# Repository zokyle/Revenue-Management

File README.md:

# Revenue-Management

Two independent FastAPI applications share this repository and its Python
dependencies:

| App | Directory | Run | What it does |
|-----|-----------|-----|--------------|
| Hotel revenue management | `app/` | `uvicorn app.main:app --reload` | demand forecasting, dynamic pricing, overbooking, PMS integrations |
| **Caddie** - golf strategy agent | `golf/` | `uvicorn golf.main:app --reload --port 8001` | learns your golf game from logged rounds and builds hole-by-hole strategies for any course, with the goal of breaking 80 |

```bash
pip install -r requirements.txt
cp .env.example .env
python scripts/seed_golf.py      # demo golfer, course and 12 rounds for the golf app
python -m pytest -q              # both apps' test suites
```

See [`golf/README.md`](golf/README.md) for how the golf agent works (with
pictures and analogies), the data-collection workflow, and the API.

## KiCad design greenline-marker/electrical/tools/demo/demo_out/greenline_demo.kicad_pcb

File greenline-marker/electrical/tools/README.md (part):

# gleda - GreenLine scripted EDA toolchain

`gleda` turns a "netlist as code" design description (Python) into a verified
KiCad 7 board.  KiCad's own DRC is the judge; nothing is reported as passing
unless KiCad says so.

The flow, each step a module that can be used on its own:

```
design script (Python)  ->  checks  ->  board  ->  router  ->  zone fill + KiCad DRC
                                                                     |
                 schematic + netlist round trip   <-   outputs (Gerber, drill, BOM,
                                                       pick-and-place, renders, JSON)
```

This file documents the design model, the checks, footprints, the board
builder, the DRC runner, the **router**, the **outputs**, the **schematic
generator** and the **demo build**, each with its limits.  Two sections are
written to be read on their own: **[Quick start: authoring a new
design](#quick-start-authoring-a-new-design)** and
**[Limitations](#limitations)** (everything the toolchain does not do, in one
place).

```
tools/
  gleda/
    model.py       design description (pure Python, no pcbnew)
    coords.py      THE design <-> KiCad coordinate conversion
    geometry.py    outline paths/polygons, placed pads, courtyards (shapely)
    footprints.py  programmatic footprints + KiCad library wrappers
    checks.py      ERC-style and placement checks
    board.py       .kicad_pcb / .kicad_pro / .kicad_dru generation, routing
                   primitives in/out, via tenting
    drc.py         zone fill + KiCad DRC + report parser + pass/fail policy
    kicad_cli.py   kicad-cli wrapper, SVG export, SVG reader
    router.py      autorouter (escape stage, negotiated routing, end game,
                   cleanup, exact audit, plane-fill prediction)
    raster.py      routing grid and exact obstacle rasterisation
    _astar.py      A* search kernel (numba-compiled when numba is installed)
    routeplot.py   quick matplotlib picture of a routed design (debug aid)
    outputs.py     Gerbers, drill, pick-and-place, BOM, netlist / mechanical JSON,
                   renders, fab README + zip - each checked against the model
    schematic.py   KiCad 7 schematic (one sheet per group), PDF, netlist round trip
  demo/
    quickstart_board.py  the smallest complete design + the whole flow (start here)
    demo_design.py     the GreenLine DEMO board (stand-in for the real GL-1)
    build_demo.py      checks -> board -> route -> DRC -> outputs -> schematic
    demo_out/          everything the last demo build produced
  tests/           pytest suite (run it from tools/)
    mini_design.py     round 30 mm fixture (castellated module, cutout, notch, slot)
    dshape_design.py   GreenLine-shaped fixture (D outline, LQFP-64, two BGAs,
                       bottom LED ring + contact row, fine net class)
    proof_core.py      builds both, KiCad DRC, plots, orientation proof
    proof_out/         outputs of the last proof run
```

## Requirements

KiCad 7.0.x with its Python module.  Always use the system interpreter:

```
cd electrical/tools
/usr/bin/python3 -m pytest -q            # test suite (about 2 minutes)
/usr/bin/python3 -m pytest -q --runslow  # ... plus the demo build from nothing (5 to 6 minutes in all)
/usr/bin/python3 demo/build_demo.py      # the whole flow on the demo board, exit 0 only if
                                         # checks, routing, KiCad DRC and round trip all pass
/usr/bin/python3 tests/proof_core.py     # build + DRC + render both reference boards
/usr/bin/python3 -m gleda.drc out/board.kicad_pcb [--allow-unconnected]
```

`pdftoppm` / `pdfinfo` (poppler-utils) turn KiCad's PDF plots into PNGs; numba
makes the router usable on real boards.  No GUI is ever started and nothing
is downloaded.

## The whole flow in one script

```python
import sys; sys.path.insert(0, "electrical/tools")
from gleda import checks, board, router, drc, outputs, schematic

design = my_design()                                    # a gleda.model.Design, see below

checks.run_checks(design).raise_if_errors()             # ERC-style + placement checks
files = board.build_board(design, "out")                # .kicad_pcb / .kicad_pro / .kicad_dru
result = router.route(design)                           # RouteResult; .complete, .unrouted
board.apply_routing(files.pcb, result.tracks, result.vias, via_tenting=design.via_tenting)
res = drc.run_drc(files.pcb, json_path="out/drc.json")  # zone fill + KiCad DRC
drc.assert_clean(res)                                   # 0 errors, 0 unconnected - or DrcError
package = outputs.generate_outputs(design, files.pcb, "out", drc_result=res, vias=result.vias)
assert package.ok, package.problems                     # plotted data == design model
sch = schematic.generate_schematic(design, "out")       # <name>.kicad_sch + one sheet per group
schematic.export_pdf(sch.root, "out/schematic.pdf")
trip = schematic.round_trip(design, sch.root)           # KiCad's netlist vs the model
assert trip.ok, trip.problems
```

`demo/build_demo.py` is exactly this with reporting around it.

## Quick start: authoring a new design

A design is one Python function that returns a `gleda.model.Design`; a second
short function takes it through the flow.  **Start from
`demo/quickstart_board.py`**: 135 lines, one 16-ball 0.5 mm BGA with its
capacitor, a pull-up and a contact row on a 24 mm D-shaped board, every step
below in the order one writes it, and a `build(design, out)` function that is
the whole flow with honest exit codes.  The test suite runs it, so it works as
written:

```
cd electrical/tools
/usr/bin/python3 demo/quickstart_board.py /some/empty/dir     # about 10 s
#   gleda checks for quickstart: 0 error(s), 0 warning(s)
#   routed 16/16 connections (100.0 %) of 10 nets, 102 tracks, 16 vias, 126.6 mm, 0 audit violation(s)
#   KiCad DRC: 0 error(s), 0 unconnected, 0 warning(s)
#   outputs: 34 files, 0 problem(s) against the model
#   netlist round trip matches: 10 nets, 26 pads, 4 components, 4 unconnected pins
```

`demo/demo_design.py` and `demo/build_demo.py` are the same thing at the size
of the real board (100 parts), with stage reporting around it.

1. **Outline and rules.**  `Outline(PathShape.d_shape(r, flat_y))` (or
   `Circle`, `RoundedPolygon`, any line + arc `PathShape`), then
   `add_hole` / `add_npth_slot` / `add_cutout`.  `Design(name, outline,
   layers=4, rules=US_4L_STD, board_thickness=0.8)`; use `US_4L_FINE` (board
   minimums 0.09 / 0.09 mm) only if a fine-pitch BGA forces it.
2. **Net classes.**  `Default` (0.15 / 0.127) and `Power` (0.30 / 0.127)
   exist.  Add `d.add_netclass("Fine", track_width=0.09, clearance=0.09)` for
   the nets on the inner balls of a 0.5 mm BGA and **declare where it may be
   fine**: `d.add_fine_area("U2", margin=5.0)`.  Outside the fine areas those
   nets are routed and DRC-checked at the standard 0.15 / 0.127 mm.  Try this
   first; if the router cannot finish that way (it cannot on the demo board),
   remove the fine areas - the fine tracks may then run anywhere on those
   nets, the checks warn, the router widens what it can, and the fab README
   tells the fab to quote the whole board at 0.09 / 0.09 mm.
3. **Parts.**  `d.add(Part(ref, value, footprint, pins=..., mpn=...,
   manufacturer=..., distributor=..., distributor_pn=..., unit_price=...,
   x=..., y=..., rotation=..., side="top" | "bottom", height_mm=...,
   group="sheet name"))`.  `footprint` is a KiCad `"Lib:Name"` string or a
   generator from `gleda.footprints` (`bga`, `quad_package`, `two_pad`,
   `pad_row`, `test_pad`, `battery_tab`, `fpc_connector`,
   `castellated_module` ...).  `pins` maps pin name -> pad number(s) and
   electrical type.  Bare pads and tabs get `in_bom=False`.
4. **Nets.**  `d.net("NAME", "U1.PA5", "R3.1", netclass="Power")`; every pin
   must be on a net, be of type `nc` or be listed in `d.no_connect(...)`.
   Supplies fed from outside the netlist get `power_flag=True`.
5. **Planes, keep-outs, mechanics.**  `d.add_plane("GND", "In1.Cu")`,
   `d.add_plane("V2V8", "In2.Cu", routable=True)` (plane and third routing
   layer), `d.add_body_keepout("U4")` (no copper under a MEMS body),
   `d.add_keepout(shape, layers=..., tracks=..., vias=..., copper=...,
   footprints=...)` (for example `tracks=False, vias=True` over a wetted
   area: no via holes there), `d.add_placement_keepout`, `d.add_height_limit`.
6. **Fab and assembly details.**  `d.via_tenting = "bottom"`,
   `d.via_protection = "plugged from the bottom side (IPC-4761 type III-a)"`,
   `d.fab_notes.append("...")`, three `d.add_fiducial(x, y, side=...)` per
   assembled side.
7. **Run the checks until they are clean**: `print(checks.run_checks(d).text())`.
   Errors stop the flow; read the warnings (`fine_unconfined`, `no_fiducials`,
   `plane_partial`, `decoupling_far` ...).
8. **Build, route, judge, export** - the script under "The whole flow in one
   script" above.  The router's result is honest (`result.complete`,
   `result.unrouted`, `result.warnings`); KiCad's DRC decides
   (`drc.assert_clean`); `outputs.generate_outputs` refuses a board that is
   not clean and verifies what it plotted against the model.

What makes a board routable by THIS router (learned on the demo, see the end
of this file): pins of a fixed-function part on the side that faces their
destination; about 1.4 x 2.0 mm per 0402 that needs a plane via; the sides of
a BGA that face the rest of the circuit kept clear for the bus escape; nothing
in the pocket between a hole and the next part; fiducials and fine areas
placed before routing (both take routing room).

**The first mistake everybody makes**: an inner ball of a 0.5 mm-pitch BGA on
a net whose class is wider than 0.09 mm (`Default`, `Power`).  Only a 0.09 mm
track with 0.09 mm clearance passes between two 0.23 mm balls, a via does not
fit between them and vias are never put in pads - so such a ball cannot be
reached, whatever net it is on, GND included.  Put every net that touches an
inner ball into a fine class (the demo: `Fine` for signals, `CamPower`
0.15 / 0.09 for supply balls on the outer ring), give the BGA pads
`pad_clearance=0.09`, and keep supplies on the outer ring where the ball map
lets you.  The router does not hang on it and does not pretend:

```
routed 15/16 connections (93.8 %) of 10 nets, 83 tracks, 15 vias, ...
OPEN D0: [['J1.3'], ['U1.B2']]  [no path from U1.B2 to J1.3]
```

A net the router leaves open is always reported like this
(`result.unrouted` -> `Unrouted.net`, `.pieces`, `.reason`; per connection in
`result.failures`) and `result.complete` is False.  Move a part or a pin,
change the class, and run again - or route that net by hand in KiCad and mark
it `no_route=True`.

## Conventions (read this first)

* Units are millimetres.  The design origin is the **board centre** (for the
  D-shaped board: the centre of the circle), **+x is right, +y is up** as seen
  from the top of the board; rotation is counter-clockwise positive.
* KiCad's y axis points down.  The conversion happens in exactly one module,
  `gleda/coords.py` (`to_kicad_mm`, `from_kicad_mm`, ...).  The board centre is
  placed at (100, 100) mm on the KiCad page and the board's auxiliary
  (drill/place) origin is set to the same point.
* Footprint-local coordinates (custom footprints, `FootprintGeom`) use the
  same handedness: +y up, looking at the component side.
* **Bottom-side parts** follow KiCad's native definition, so `Part.rotation`
  is the number KiCad stores, shows and writes to position files:
  the footprint is flipped about its local X axis and then rotated CCW as
  seen from the top:

      top:     board = (x, y) + R(rotation) . (lx,  ly)
      bottom:  board = (x, y) + R(rotation) . (lx, -ly)

  `coords.local_to_board()` implements this and
  `tests/test_board.py::test_pads_match_model_geometry` proves that every pad
  position predicted by the model equals what pcbnew reports for the saved
  board.  `tests/test_board.py::test_top_view_svg_has_plus_y_up` proves from a
  KiCad SVG plot that a part placed at +y is drawn toward the top.

## Describing a design

```python
from gleda.model import (Design, Outline, Circle, RoundedPolygon, PathShape, Part,
                         two_pin, n_pin, US_4L_FINE, BOTTOM)
from gleda import footprints as F

# circle r = 21.2 mm about the origin, clipped by the chord y = +17.3 mm
outline = Outline(PathShape.d_shape(21.2, 17.3))
# also: Outline(Circle(0, 0, 19.0)), RoundedPolygon(...), any line + arc path:
#   PathShape.begin(-5, 0).line_to(5, 0).arc_to(-5, 0, 0, 0, ccw=True).close()
#   PathShape.clipped_circle(0, 0, 21.2, [(90, 17.3), (270, 19.0)])
outline.add_cutout(Circle(9.0, 0.0, 6.5))              # internal routed cutout
outline.add_notch(RoundedPolygon.rect(0, -21.2, 3, 2, 0.4))   # crosses the edge
outline.add_slot(-6, -11, -4, -11, 0.8)
outline.add_hole(-12, 5, 1.2)                          # NPTH

d = Design("greenline", outline, layers=4, rules=US_4L_FINE, board_thickness=0.8)
d.add_netclass("Fine", track_width=0.09, clearance=0.09)   # BGA escape only
d.via_tenting = "bottom"                               # "both" (default) | "bottom" | "top" | "none"
d.via_protection = "plugged from the bottom side (IPC-4761 type III-a)"   # -> fab README
d.fab_notes.append("The bottom side is a wetted surface: no open via holes there.")

cam = F.bga("Cam_BGA25", 5, 5, pitch=0.5, pad_d=0.23, body=(3.47, 2.95), height=2.76,
            pad_clearance=0.09, courtyard_margin=0.2)
d.add(Part("U2", "Camera", cam,
           pins={"D0": ("B2", "bidir"), "AVDD": ("C5", "power_in"),
                 "GND": (("E2", "E3", "E4"), "power_in"), "NC": ("A1", "nc")},  # ... all balls
           mpn="...", manufacturer="...", distributor="Digi-Key", distributor_pn="...",
           unit_price=6.0, x=-10.2, y=15.6, rotation=0, side="top", height_mm=2.76,
           group="camera"))
d.add(Part("C1", "100n", "Capacitor_SMD:C_0402_1005Metric", pins=two_pin(),
           mpn="...", x=-7.2, y=15.3, rotation=90, group="camera"))
d.add(Part("J2", "Cradle pads", F.pad_row("ContactRow", 7, 2.54, 1.8), pins=n_pin(7),
           x=0, y=-17.0, side=BOTTOM, in_bom=False))    # bare pads on the bottom

d.net("GND", "U2.GND", "C1.2", "J2.4", netclass="Power")
d.net("V2V8", "U2.AVDD", "C1.1", netclass="Power", power_flag=True)
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
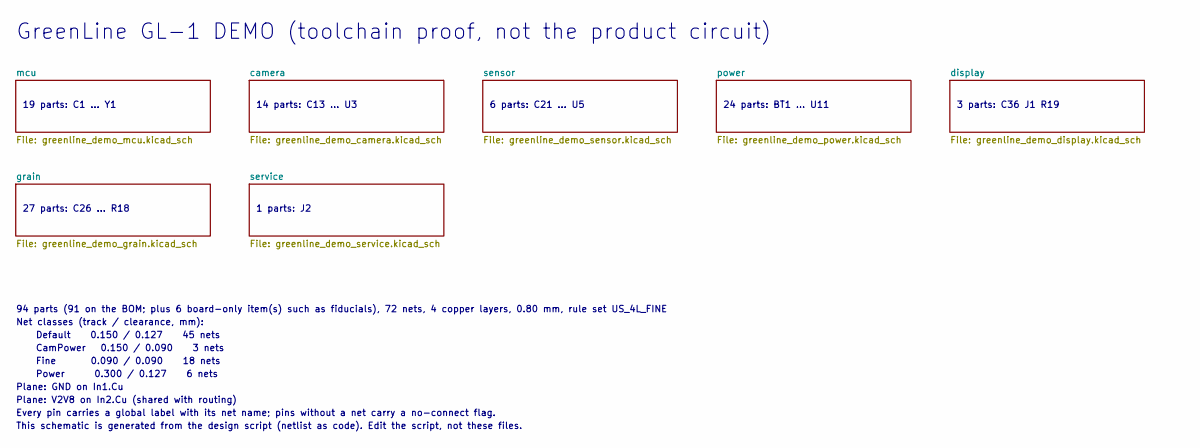
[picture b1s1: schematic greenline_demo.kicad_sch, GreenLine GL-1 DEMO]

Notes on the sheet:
GreenLine GL-1 DEMO (toolchain proof, not the product circuit)
19 parts: C1 ... Y1
14 parts: C13 ... U3
6 parts: C21 ... U5
24 parts: BT1 ... U11
3 parts: C36 J1 R19
27 parts: C26 ... R18
1 parts: J2
94 parts (91 on the BOM; plus 6 board-only item(s) such as fiducials), 72 nets, 4 copper layers, 0.80 mm, rule set US_4L_FINE
Net classes (track / clearance, mm):
Default 0.150 / 0.127 45 nets
CamPower 0.150 / 0.090 3 nets
Fine 0.090 / 0.090 18 nets
Power 0.300 / 0.127 6 nets
Plane: GND on In1.Cu
Plane: V2V8 on In2.Cu (shared with routing)
Every pin carries a global label with its net name; pins without a net carry a no-connect flag.
This schematic is generated from the design script (netlist as code). Edit the script, not these files.

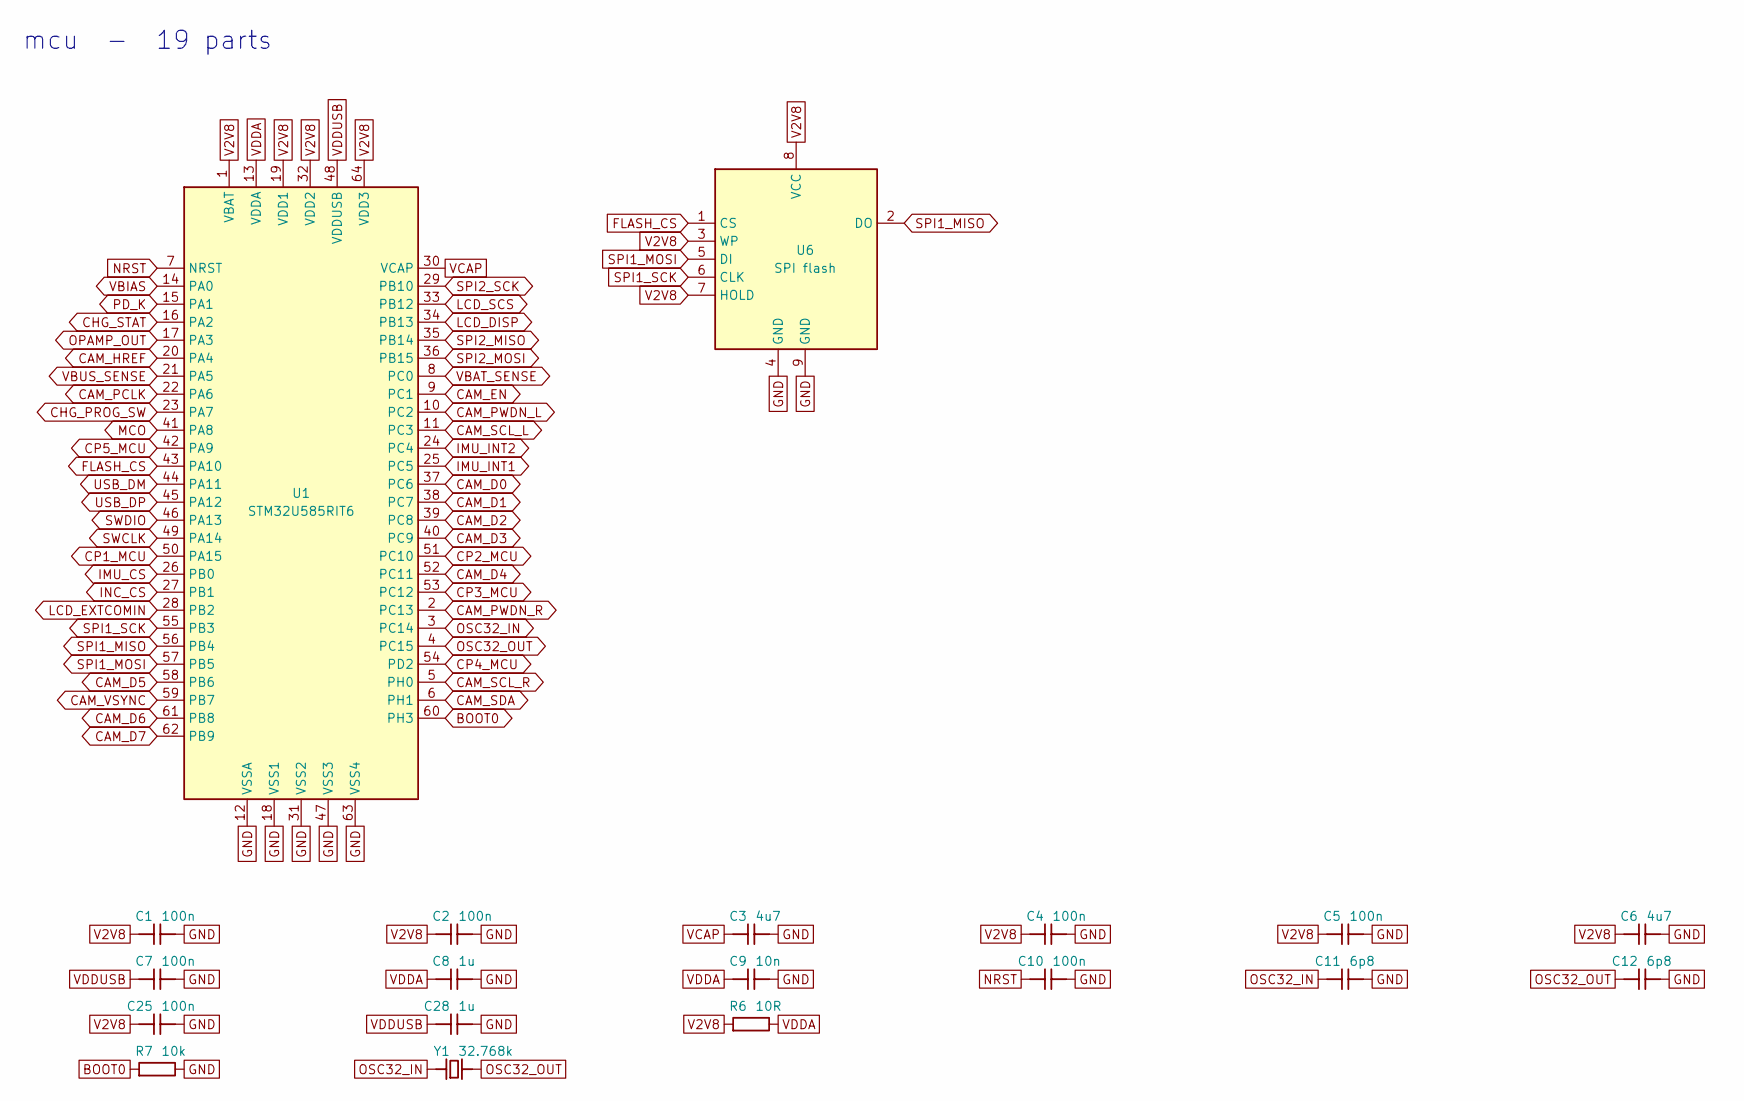
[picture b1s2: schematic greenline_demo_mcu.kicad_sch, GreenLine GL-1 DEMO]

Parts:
C1, C2, C4, C5, C7, C10, C25: 100n; C_0402_1005Metric; MPN GRM155R71C104KA88D
C3, C6: 4u7; C_0402_1005Metric; MPN GRM155R60J475ME47D
C8, C28: 1u; C_0402_1005Metric; MPN GRM155R61A105KE15D
C9: 10n; C_0402_1005Metric; MPN GRM155R71H103KA88D
C11, C12: 6p8; C_0402_1005Metric; MPN GRM1555C1H6R8CA01D
R6: 10R; R_0402_1005Metric; MPN RC0402FR-0710RL
R7: 10k; R_0402_1005Metric; MPN RC0402FR-0710KL
U1: STM32U585RIT6; LQFP-64_10x10mm_P0.5mm; MPN STM32U585RIT6
U6: SPI flash; WSON-8-1EP_6x5mm_P1.27mm_EP3.4x4.3mm; MPN MX25R6435FZNIL0
Y1: 32.768k; Crystal_SMD_3215-2Pin_3.2x1.5mm; MPN ABS07-120-32.768KHZ-T

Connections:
BOOT0: R7.1, U1.60 (PH3)
CAM_D0: U1.37 (PC6); also elsewhere on the board
CAM_D1: U1.38 (PC7); also elsewhere on the board
CAM_D2: U1.39 (PC8); also elsewhere on the board
CAM_D3: U1.40 (PC9); also elsewhere on the board
CAM_D4: U1.52 (PC11); also elsewhere on the board
CAM_D5: U1.58 (PB6); also elsewhere on the board
CAM_D6: U1.61 (PB8); also elsewhere on the board
CAM_D7: U1.62 (PB9); also elsewhere on the board
CAM_EN: U1.9 (PC1); also elsewhere on the board
CAM_HREF: U1.20 (PA4); also elsewhere on the board
CAM_PCLK: U1.22 (PA6); also elsewhere on the board
CAM_PWDN_L: U1.10 (PC2); also elsewhere on the board
CAM_PWDN_R: U1.2 (PC13); also elsewhere on the board
CAM_SCL_L: U1.11 (PC3); also elsewhere on the board
CAM_SCL_R: U1.5 (PH0); also elsewhere on the board
CAM_SDA: U1.6 (PH1); also elsewhere on the board
CAM_VSYNC: U1.59 (PB7); also elsewhere on the board
CHG_PROG_SW: U1.23 (PA7); also elsewhere on the board
CHG_STAT: U1.16 (PA2); also elsewhere on the board
CP1_MCU: U1.50 (PA15); also elsewhere on the board
CP2_MCU: U1.51 (PC10); also elsewhere on the board
CP3_MCU: U1.53 (PC12); also elsewhere on the board
CP4_MCU: U1.54 (PD2); also elsewhere on the board
CP5_MCU: U1.42 (PA9); also elsewhere on the board
FLASH_CS: U1.43 (PA10), U6.1 (CS)
GND: C1.2, C2.2, C3.2, C4.2, C5.2, C6.2, C7.2, C8.2, C9.2, C10.2, C11.2, C12.2, C25.2, C28.2, R7.2, U1.12 (VSSA), U1.18 (VSS1), U1.31 (VSS2), U1.47 (VSS3), U1.63 (VSS4), U6.4 (GND), U6.9 (GND); also elsewhere on the board
IMU_CS: U1.26 (PB0); also elsewhere on the board
IMU_INT1: U1.25 (PC5); also elsewhere on the board
IMU_INT2: U1.24 (PC4); also elsewhere on the board
INC_CS: U1.27 (PB1); also elsewhere on the board
LCD_DISP: U1.34 (PB13); also elsewhere on the board
LCD_EXTCOMIN: U1.28 (PB2); also elsewhere on the board
LCD_SCS: U1.33 (PB12); also elsewhere on the board
MCO: U1.41 (PA8); also elsewhere on the board
NRST: C10.1, U1.7 (NRST); also elsewhere on the board
OPAMP_OUT: U1.17 (PA3); also elsewhere on the board
OSC32_IN: C11.1, U1.3 (PC14), Y1.1
OSC32_OUT: C12.1, U1.4 (PC15), Y1.2
PD_K: U1.15 (PA1); also elsewhere on the board
SPI1_MISO: U1.56 (PB4), U6.2 (DO)
SPI1_MOSI: U1.57 (PB5), U6.5 (DI); also elsewhere on the board
SPI1_SCK: U1.55 (PB3), U6.6 (CLK); also elsewhere on the board
SPI2_MISO: U1.35 (PB14); also elsewhere on the board
SPI2_MOSI: U1.36 (PB15); also elsewhere on the board
SPI2_SCK: U1.29 (PB10); also elsewhere on the board
SWCLK: U1.49 (PA14); also elsewhere on the board
SWDIO: U1.46 (PA13); also elsewhere on the board
USB_DM: U1.44 (PA11); also elsewhere on the board
USB_DP: U1.45 (PA12); also elsewhere on the board
V2V8: C1.1, C2.1, C4.1, C5.1, C6.1, C25.1, R6.1, U1.1 (VBAT), U1.19 (VDD1), U1.32 (VDD2), U1.64 (VDD3), U6.3 (WP), U6.7 (HOLD), U6.8 (VCC); also elsewhere on the board
VBAT_SENSE: U1.8 (PC0); also elsewhere on the board
VBIAS: U1.14 (PA0); also elsewhere on the board
VBUS_SENSE: U1.21 (PA5); also elsewhere on the board
VCAP: C3.1, U1.30 (VCAP)
VDDA: C8.1, C9.1, R6.2, U1.13 (VDDA)
VDDUSB: C7.1, C28.1, U1.48 (VDDUSB); also elsewhere on the board

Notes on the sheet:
mcu - 19 parts

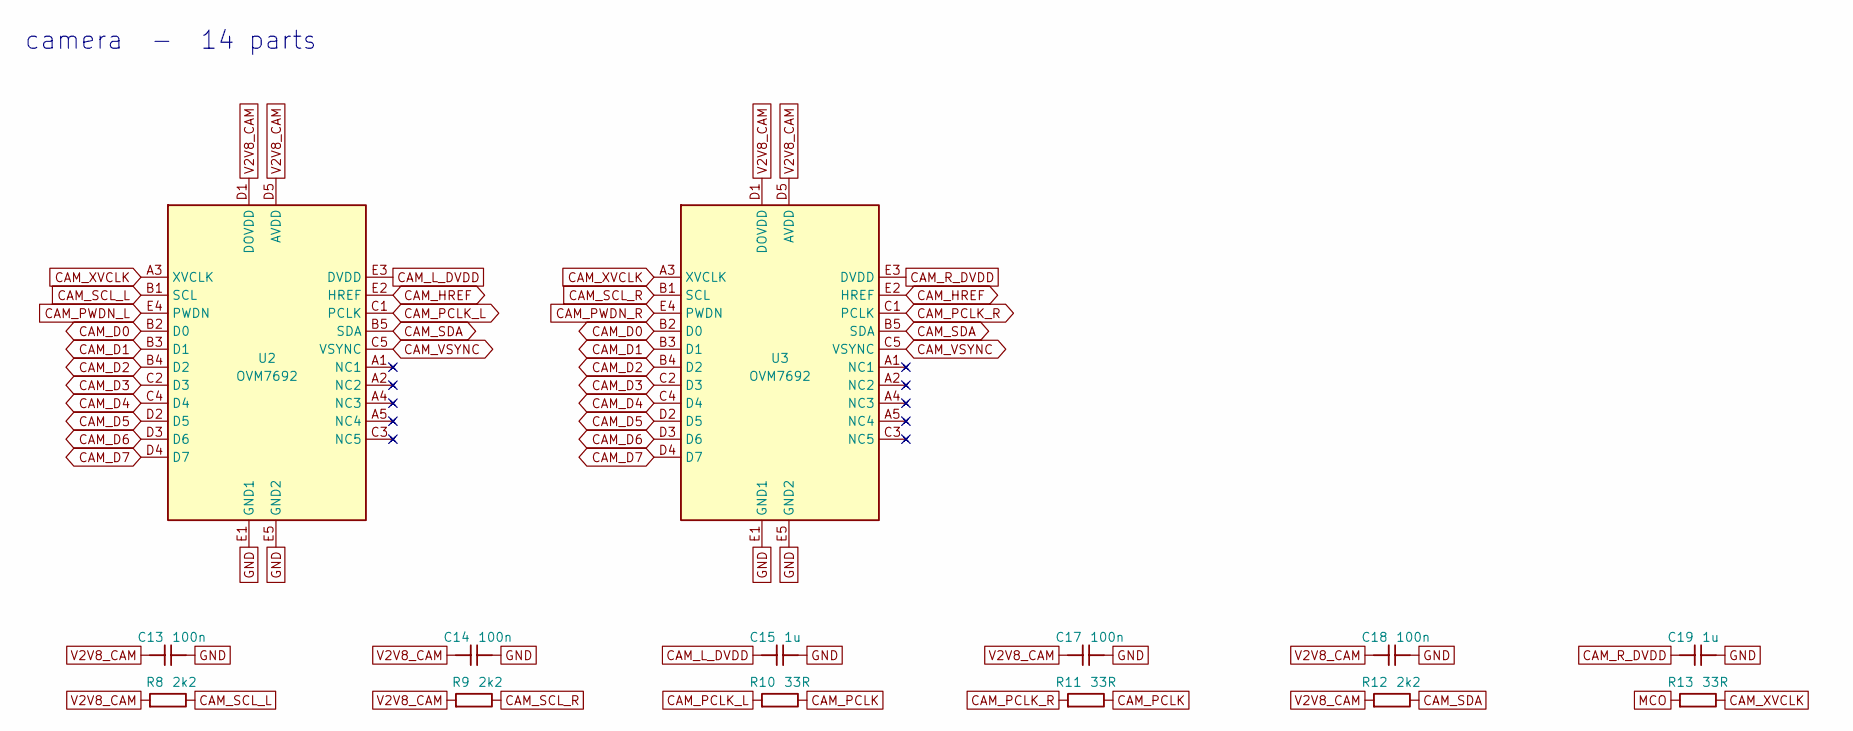
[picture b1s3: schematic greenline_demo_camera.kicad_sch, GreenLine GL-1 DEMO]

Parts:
C13, C14, C17, C18: 100n; C_0402_1005Metric; MPN GRM155R71C104KA88D
C15, C19: 1u; C_0402_1005Metric; MPN GRM155R61A105KE15D
R8, R9, R12: 2k2; R_0402_1005Metric; MPN RC0402FR-072K2L
R10, R11, R13: 33R; R_0402_1005Metric; MPN RC0402FR-0733RL
U2, U3: OVM7692; CamCube_BGA25_P0.5; MPN OVM7692-RYAA

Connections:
CAM_D0: U2.B2 (D0), U3.B2 (D0); also elsewhere on the board
CAM_D1: U2.B3 (D1), U3.B3 (D1); also elsewhere on the board
CAM_D2: U2.B4 (D2), U3.B4 (D2); also elsewhere on the board
CAM_D3: U2.C2 (D3), U3.C2 (D3); also elsewhere on the board
CAM_D4: U2.C4 (D4), U3.C4 (D4); also elsewhere on the board
CAM_D5: U2.D2 (D5), U3.D2 (D5); also elsewhere on the board
CAM_D6: U2.D3 (D6), U3.D3 (D6); also elsewhere on the board
CAM_D7: U2.D4 (D7), U3.D4 (D7); also elsewhere on the board
CAM_HREF: U2.E2 (HREF), U3.E2 (HREF); also elsewhere on the board
CAM_L_DVDD: C15.1, U2.E3 (DVDD)
CAM_PCLK: R10.2, R11.2; also elsewhere on the board
CAM_PCLK_L: R10.1, U2.C1 (PCLK)
CAM_PCLK_R: R11.1, U3.C1 (PCLK)
CAM_PWDN_L: U2.E4 (PWDN); also elsewhere on the board
CAM_PWDN_R: U3.E4 (PWDN); also elsewhere on the board
CAM_R_DVDD: C19.1, U3.E3 (DVDD)
CAM_SCL_L: R8.2, U2.B1 (SCL); also elsewhere on the board
CAM_SCL_R: R9.2, U3.B1 (SCL); also elsewhere on the board
CAM_SDA: R12.2, U2.B5 (SDA), U3.B5 (SDA); also elsewhere on the board
CAM_VSYNC: U2.C5 (VSYNC), U3.C5 (VSYNC); also elsewhere on the board
CAM_XVCLK: R13.2, U2.A3 (XVCLK), U3.A3 (XVCLK)
GND: C13.2, C14.2, C15.2, C17.2, C18.2, C19.2, U2.E1 (GND1), U2.E5 (GND2), U3.E1 (GND1), U3.E5 (GND2); also elsewhere on the board
MCO: R13.1; also elsewhere on the board
V2V8_CAM: C13.1, C14.1, C17.1, C18.1, R8.1, R9.1, R12.1, U2.D1 (DOVDD), U2.D5 (AVDD), U3.D1 (DOVDD), U3.D5 (AVDD); also elsewhere on the board

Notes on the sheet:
camera - 14 parts

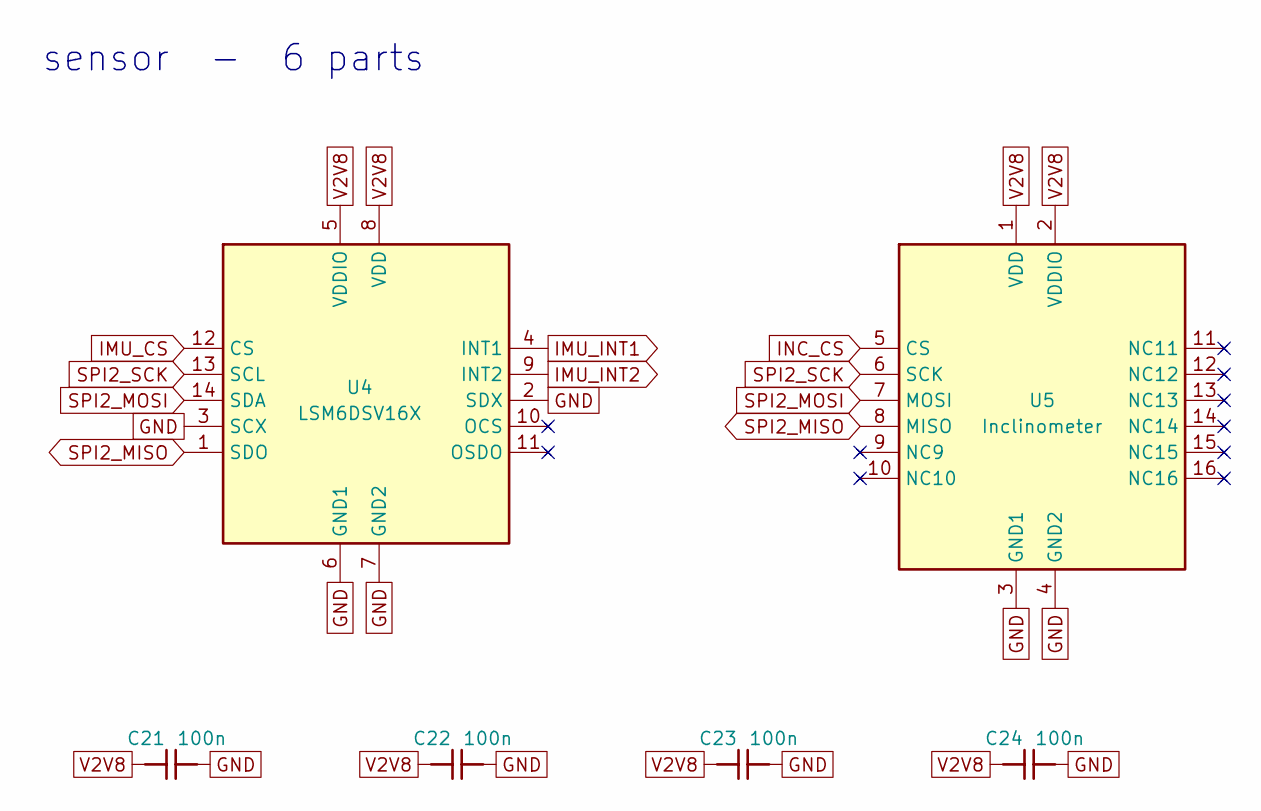
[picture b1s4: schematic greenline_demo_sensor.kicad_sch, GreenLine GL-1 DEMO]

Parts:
C21, C22, C23, C24: 100n; C_0402_1005Metric; MPN GRM155R71C104KA88D
U4: LSM6DSV16X; LGA-14_3x2.5mm_P0.5mm_LayoutBorder3x4y; MPN LSM6DSV16XTR
U5: Inclinometer; LGA-16_5x5mm_P1.0mm; MPN IIS2ICLXTR

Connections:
GND: C21.2, C22.2, C23.2, C24.2, U4.2 (SDX), U4.3 (SCX), U4.6 (GND1), U4.7 (GND2), U5.3 (GND1), U5.4 (GND2); also elsewhere on the board
IMU_CS: U4.12 (CS); also elsewhere on the board
IMU_INT1: U4.4 (INT1); also elsewhere on the board
IMU_INT2: U4.9 (INT2); also elsewhere on the board
INC_CS: U5.5 (CS); also elsewhere on the board
SPI2_MISO: U4.1 (SDO), U5.8 (MISO); also elsewhere on the board
SPI2_MOSI: U4.14 (SDA), U5.7 (MOSI); also elsewhere on the board
SPI2_SCK: U4.13 (SCL), U5.6 (SCK); also elsewhere on the board
V2V8: C21.1, C22.1, C23.1, C24.1, U4.5 (VDDIO), U4.8 (VDD), U5.1 (VDD), U5.2 (VDDIO); also elsewhere on the board

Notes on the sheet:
sensor - 6 parts

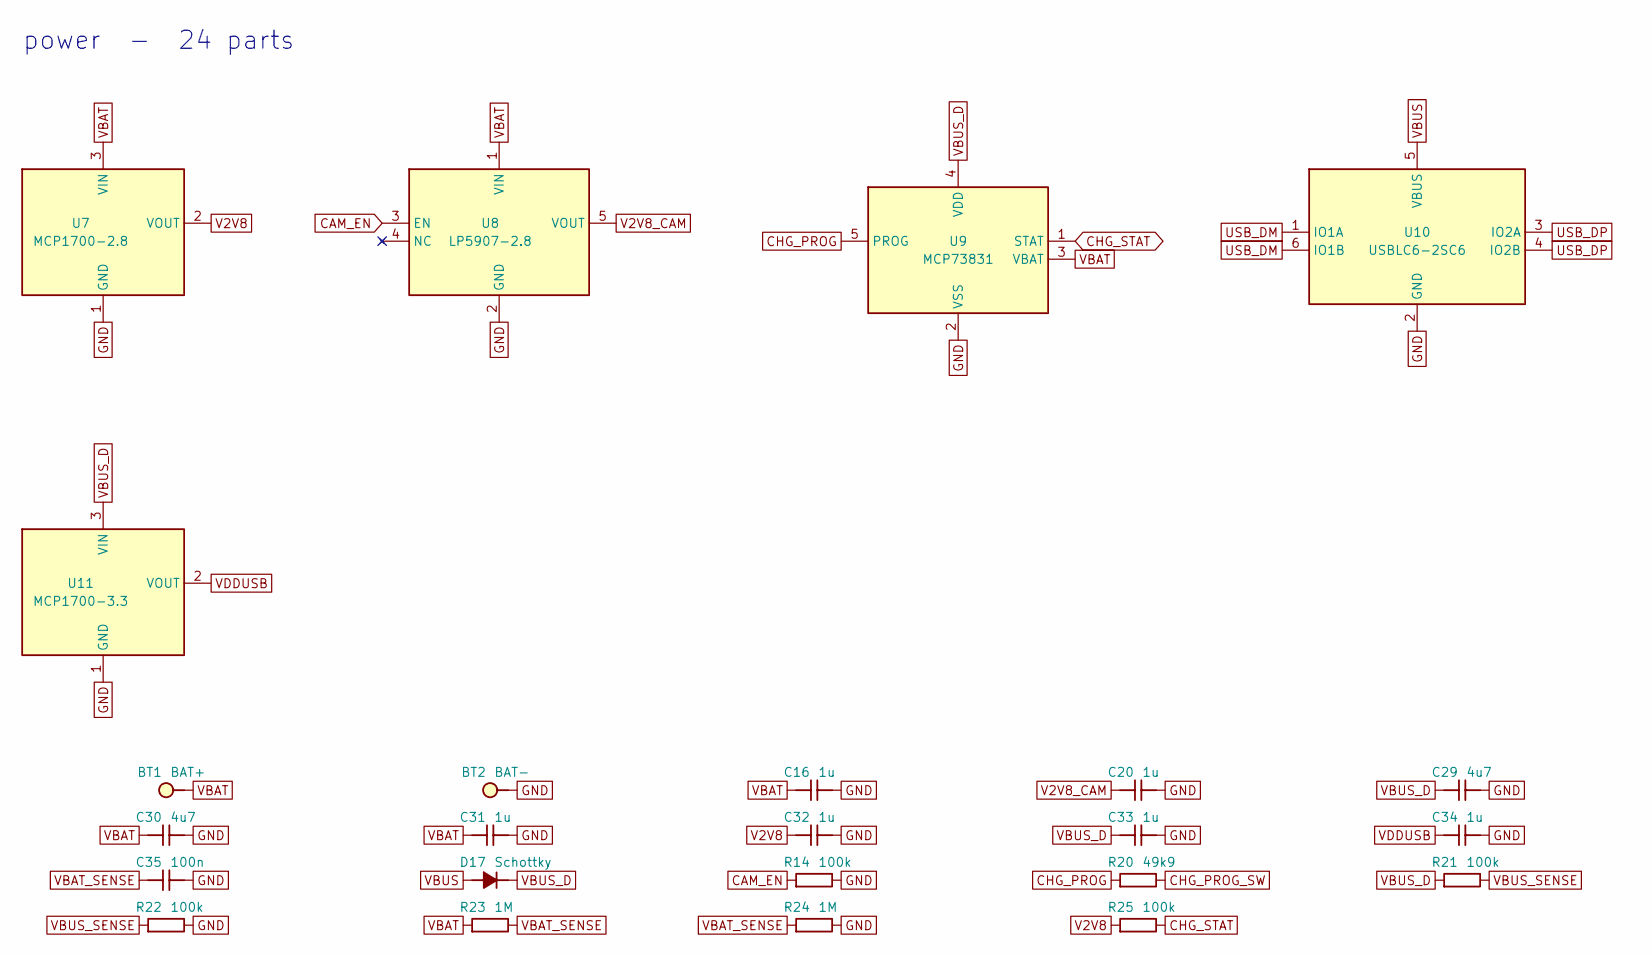
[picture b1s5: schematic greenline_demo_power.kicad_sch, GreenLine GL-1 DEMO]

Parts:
BT1: BAT+; BatteryTab_1.2x2mm
BT2: BAT-; BatteryTab_1.2x2mm
C16, C20, C31, C32, C33, C34: 1u; C_0402_1005Metric; MPN GRM155R61A105KE15D
C29, C30: 4u7; C_0402_1005Metric; MPN GRM155R60J475ME47D
C35: 100n; C_0402_1005Metric; MPN GRM155R71C104KA88D
D17: Schottky; D_SOD-323; MPN BAT60JFILM
R14, R21, R22, R25: 100k; R_0402_1005Metric; MPN RC0402FR-07100KL
R20: 49k9; R_0402_1005Metric; MPN RC0402FR-0749K9L
R23, R24: 1M; R_0402_1005Metric; MPN RC0402FR-071ML
U7: MCP1700-2.8; SOT-23; MPN MCP1700T-2802E/TT
U8: LP5907-2.8; SOT-23-5; MPN LP5907MFX-2.8/NOPB
U9: MCP73831; SOT-23-5; MPN MCP73831T-2ACI/OT
U10: USBLC6-2SC6; SOT-23-6; MPN USBLC6-2SC6
U11: MCP1700-3.3; SOT-23; MPN MCP1700T-3302E/TT

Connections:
CAM_EN: R14.1, U8.3 (EN); also elsewhere on the board
CHG_PROG: R20.1, U9.5 (PROG)
CHG_PROG_SW: R20.2; also elsewhere on the board
CHG_STAT: R25.2, U9.1 (STAT); also elsewhere on the board
GND: BT2.1, C16.2, C20.2, C29.2, C30.2, C31.2, C32.2, C33.2, C34.2, C35.2, R14.2, R22.2, R24.2, U7.1 (GND), U8.2 (GND), U9.2 (VSS), U10.2 (GND), U11.1 (GND); also elsewhere on the board
USB_DM: U10.1 (IO1A), U10.6 (IO1B); also elsewhere on the board
USB_DP: U10.3 (IO2A), U10.4 (IO2B); also elsewhere on the board
V2V8: C32.1, R25.1, U7.2 (VOUT); also elsewhere on the board
V2V8_CAM: C20.1, U8.5 (VOUT); also elsewhere on the board
VBAT: BT1.1, C16.1, C30.1, C31.1, R23.1, U7.3 (VIN), U8.1 (VIN), U9.3 (VBAT)
VBAT_SENSE: C35.1, R23.2, R24.1; also elsewhere on the board
VBUS: D17.2 (A), U10.5 (VBUS); also elsewhere on the board
VBUS_D: C29.1, C33.1, D17.1 (K), R21.1, U9.4 (VDD), U11.3 (VIN)
VBUS_SENSE: R21.2, R22.1; also elsewhere on the board
VDDUSB: C34.1, U11.2 (VOUT); also elsewhere on the board

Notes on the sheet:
power - 24 parts

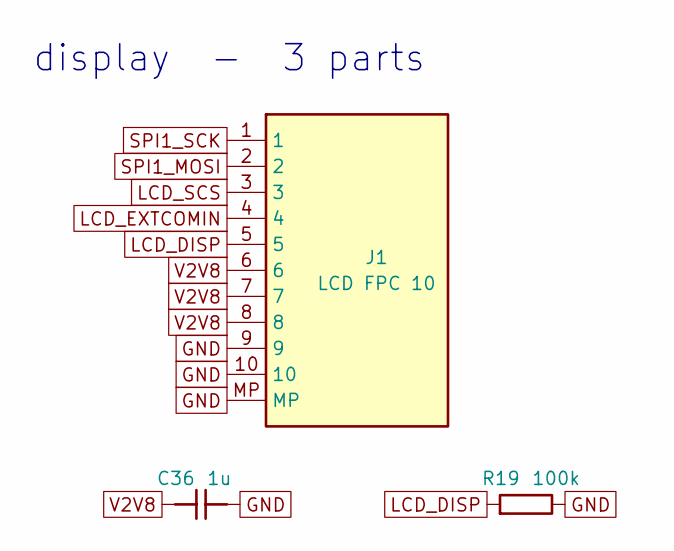
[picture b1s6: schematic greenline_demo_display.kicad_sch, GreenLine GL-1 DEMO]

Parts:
C36: 1u; C_0402_1005Metric; MPN GRM155R61A105KE15D
J1: LCD FPC 10; Hirose_FH12-10S-0.5SH_1x10-1MP_P0.50mm_Horizontal; MPN FH12A-10S-0.5SH(55)
R19: 100k; R_0402_1005Metric; MPN RC0402FR-07100KL

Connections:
GND: C36.2, J1.9, J1.10, J1.MP, R19.2; also elsewhere on the board
LCD_DISP: J1.5, R19.1; also elsewhere on the board
LCD_EXTCOMIN: J1.4; also elsewhere on the board
LCD_SCS: J1.3; also elsewhere on the board
SPI1_MOSI: J1.2; also elsewhere on the board
SPI1_SCK: J1.1; also elsewhere on the board
V2V8: C36.1, J1.6, J1.7, J1.8; also elsewhere on the board

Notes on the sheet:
display - 3 parts

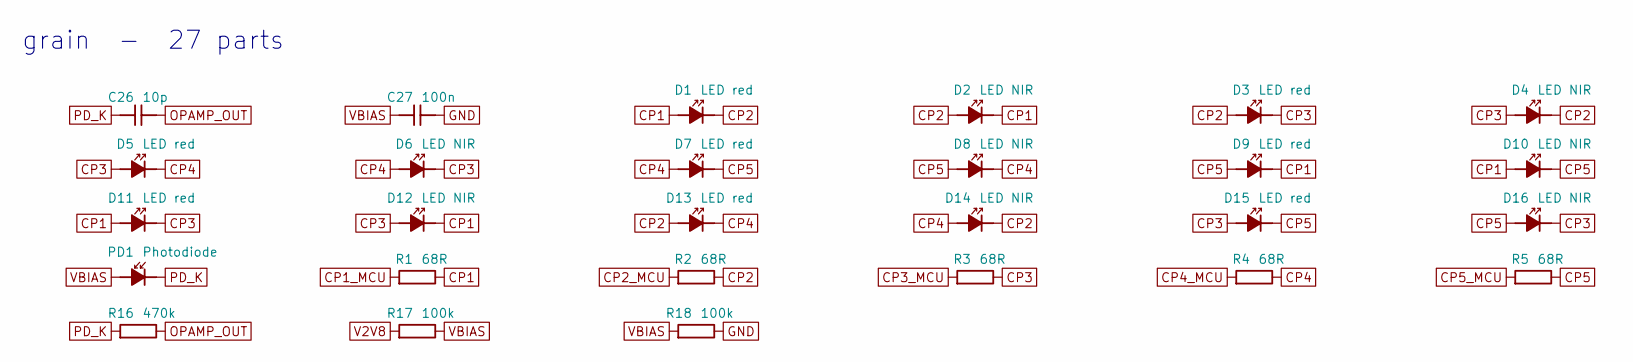
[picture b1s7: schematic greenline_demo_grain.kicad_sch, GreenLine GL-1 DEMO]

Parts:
C26: 10p; C_0402_1005Metric; MPN GRM1555C1H100JA01D
C27: 100n; C_0402_1005Metric; MPN GRM155R71C104KA88D
D1, D3, D5, D7, D9, D11, D13, D15: LED red; LED_0402_1005Metric; MPN APHHS1005SURCK
D2, D4, D6, D8, D10, D12, D14, D16: LED NIR; LED_0402_1005Metric; MPN APHHS1005F3C
PD1: Photodiode; Photodiode_4.8x2.5mm; MPN VEMD5510C
R1, R2, R3, R4, R5: 68R; R_0402_1005Metric; MPN RC0402FR-0768RL
R16: 470k; R_0402_1005Metric; MPN RC0402FR-07470KL
R17, R18: 100k; R_0402_1005Metric; MPN RC0402FR-07100KL

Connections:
CP1: D1.2 (A), D2.1 (K), D9.1 (K), D10.2 (A), D11.2 (A), D12.1 (K), R1.2
CP1_MCU: R1.1; also elsewhere on the board
CP2: D1.1 (K), D2.2 (A), D3.2 (A), D4.1 (K), D13.2 (A), D14.1 (K), R2.2
CP2_MCU: R2.1; also elsewhere on the board
CP3: D3.1 (K), D4.2 (A), D5.2 (A), D6.1 (K), D11.1 (K), D12.2 (A), D15.2 (A), D16.1 (K), R3.2
CP3_MCU: R3.1; also elsewhere on the board
CP4: D5.1 (K), D6.2 (A), D7.2 (A), D8.1 (K), D13.1 (K), D14.2 (A), R4.2
CP4_MCU: R4.1; also elsewhere on the board
CP5: D7.1 (K), D8.2 (A), D9.2 (A), D10.1 (K), D15.1 (K), D16.2 (A), R5.2
CP5_MCU: R5.1; also elsewhere on the board
GND: C27.2, R18.2; also elsewhere on the board
OPAMP_OUT: C26.2, R16.2; also elsewhere on the board
PD_K: C26.1, PD1.K, R16.1; also elsewhere on the board
V2V8: R17.1; also elsewhere on the board
VBIAS: C27.1, PD1.A, R17.2, R18.1; also elsewhere on the board

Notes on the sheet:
grain - 27 parts

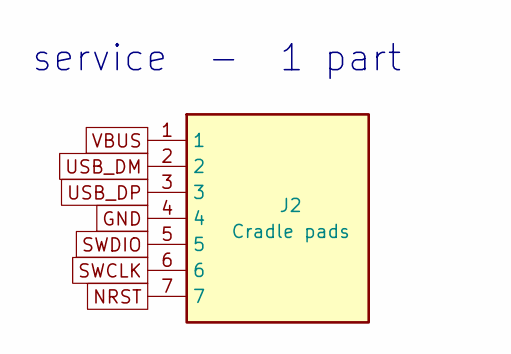
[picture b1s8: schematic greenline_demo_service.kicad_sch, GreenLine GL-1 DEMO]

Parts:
J2: Cradle pads; ContactRow_7x1.8mm_P2.54

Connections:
GND: J2.4; also elsewhere on the board
NRST: J2.7; also elsewhere on the board
SWCLK: J2.6; also elsewhere on the board
SWDIO: J2.5; also elsewhere on the board
USB_DM: J2.2; also elsewhere on the board
USB_DP: J2.3; also elsewhere on the board
VBUS: J2.1; also elsewhere on the board

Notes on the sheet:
service - 1 part

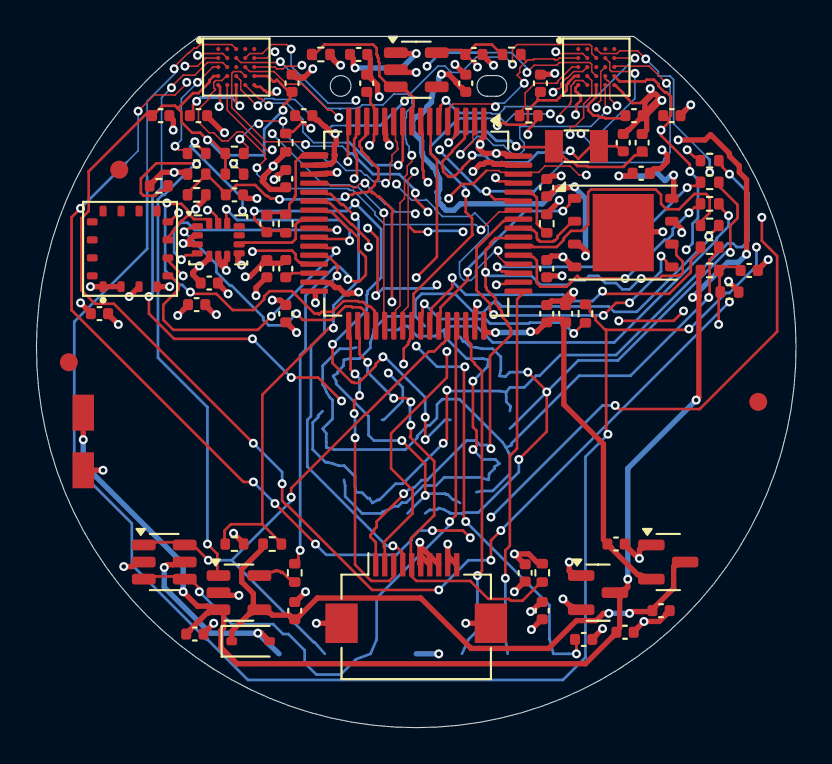
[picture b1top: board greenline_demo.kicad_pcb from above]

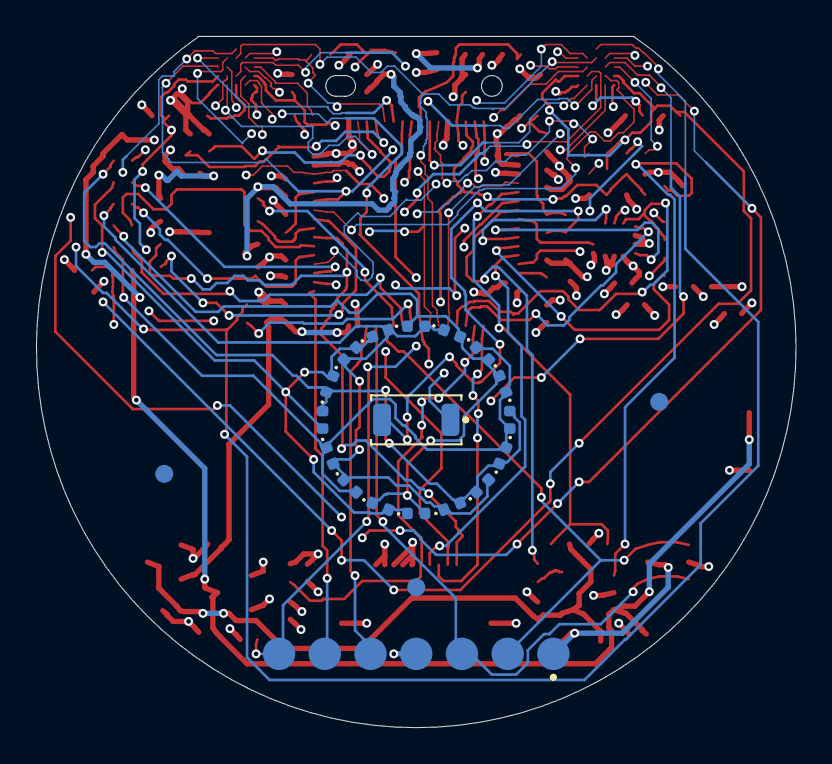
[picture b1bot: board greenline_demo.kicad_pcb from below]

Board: 4 copper layers, 42.2 x 38.4 mm, 101 parts (21 on the bottom side), 72 nets.

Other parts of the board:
FID1, FID2, FID3, FID4, FID5, FID6: Fiducial; Fiducial_1mm_Mask2mm
H1: NPTH 1.15mm; NPTH_1.15mm

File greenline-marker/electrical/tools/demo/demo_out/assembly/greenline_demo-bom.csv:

Item,Qty,References,Value,Description,Footprint,MPN,Manufacturer,Distributor,Distributor PN,Unit Price,Extended Price,DNP
1,17,C1 C2 C4 C5 C7 C10 C13 C14 C17 C18 C21 C22 C23 C24 C25 C27 C35,100n,MLCC 0402 100n,Capacitor_SMD:C_0402_1005Metric,GRM155R71C104KA88D,Murata,Digi-Key,490-3261-1-ND,0.0200,0.3400,
2,4,C3 C6 C29 C30,4u7,MLCC 0402 4u7,Capacitor_SMD:C_0402_1005Metric,GRM155R60J475ME47D,Murata,Digi-Key,490-5915-1-ND,0.0600,0.2400,
3,11,C8 C15 C16 C19 C20 C28 C31 C32 C33 C34 C36,1u,MLCC 0402 1u,Capacitor_SMD:C_0402_1005Metric,GRM155R61A105KE15D,Murata,Digi-Key,490-3890-1-ND,0.0300,0.3300,
4,1,C9,10n,MLCC 0402 10n,Capacitor_SMD:C_0402_1005Metric,GRM155R71H103KA88D,Murata,Digi-Key,490-1312-1-ND,0.0200,0.0200,
5,2,C11 C12,6p8,MLCC 0402 6p8,Capacitor_SMD:C_0402_1005Metric,GRM1555C1H6R8CA01D,Murata,Digi-Key,490-5947-1-ND,0.0300,0.0600,
6,1,C26,10p,MLCC 0402 10p,Capacitor_SMD:C_0402_1005Metric,GRM1555C1H100JA01D,Murata,Digi-Key,490-5921-1-ND,0.0300,0.0300,
7,8,D1 D3 D5 D7 D9 D11 D13 D15,LED red,grain LED 0402,LED_SMD:LED_0402_1005Metric,APHHS1005SURCK,Kingbright,Digi-Key,754-1104-1-ND,0.3500,2.8000,
8,8,D2 D4 D6 D8 D10 D12 D14 D16,LED NIR,grain LED 0402,LED_SMD:LED_0402_1005Metric,APHHS1005F3C,Kingbright,Digi-Key,754-1105-1-ND,0.3500,2.8000,
9,1,D17,Schottky,VBUS series Schottky,Diode_SMD:D_SOD-323,BAT60JFILM,STMicroelectronics,Digi-Key,497-3707-1-ND,0.3000,0.3000,
10,1,J1,LCD FPC 10,"LCD FPC connector, 10 x 0.5 mm",Connector_FFC-FPC:Hirose_FH12-10S-0.5SH_1x10-1MP_P0.50mm_Horizontal,FH12A-10S-0.5SH(55),Hirose,Digi-Key,HFJ110CT-ND,0.9000,0.9000,
11,1,PD1,Photodiode,photodiode (stand-in land pattern),gleda:Photodiode_4.8x2.5mm,VEMD5510C,Vishay,Digi-Key,VEMD5510CCT-ND,1.2000,1.2000,
12,5,R1 R2 R3 R4 R5,68R,Resistor 0402 1% 68R,Resistor_SMD:R_0402_1005Metric,RC0402FR-0768RL,Yageo,Digi-Key,RC0402FR-0768RL-ND,0.0100,0.0500,
13,1,R6,10R,Resistor 0402 1% 10R,Resistor_SMD:R_0402_1005Metric,RC0402FR-0710RL,Yageo,Digi-Key,RC0402FR-0710RL-ND,0.0100,0.0100,
14,1,R7,10k,Resistor 0402 1% 10k,Resistor_SMD:R_0402_1005Metric,RC0402FR-0710KL,Yageo,Digi-Key,RC0402FR-0710KL-ND,0.0100,0.0100,
15,3,R8 R9 R12,2k2,Resistor 0402 1% 2k2,Resistor_SMD:R_0402_1005Metric,RC0402FR-072K2L,Yageo,Digi-Key,RC0402FR-072K2L-ND,0.0100,0.0300,
16,3,R10 R11 R13,33R,Resistor 0402 1% 33R,Resistor_SMD:R_0402_1005Metric,RC0402FR-0733RL,Yageo,Digi-Key,RC0402FR-0733RL-ND,0.0100,0.0300,
17,7,R14 R17 R18 R19 R21 R22 R25,100k,Resistor 0402 1% 100k,Resistor_SMD:R_0402_1005Metric,RC0402FR-07100KL,Yageo,Digi-Key,RC0402FR-07100KL-ND,0.0100,0.0700,
18,1,R16,470k,Resistor 0402 1% 470k,Resistor_SMD:R_0402_1005Metric,RC0402FR-07470KL,Yageo,Digi-Key,RC0402FR-07470KL-ND,0.0100,0.0100,
19,1,R20,49k9,Resistor 0402 1% 49k9,Resistor_SMD:R_0402_1005Metric,RC0402FR-0749K9L,Yageo,Digi-Key,RC0402FR-0749K9L-ND,0.0100,0.0100,
20,2,R23 R24,1M,Resistor 0402 1% 1M,Resistor_SMD:R_0402_1005Metric,RC0402FR-071ML,Yageo,Digi-Key,RC0402FR-071ML-ND,0.0100,0.0200,
21,1,U1,STM32U585RIT6,"MCU, LQFP-64",Package_QFP:LQFP-64_10x10mm_P0.5mm,STM32U585RIT6,STMicroelectronics,Digi-Key,497-STM32U585RIT6-ND,9.5000,9.5000,
22,2,U2 U3,OVM7692,camera cube (stand-in ball map),gleda:CamCube_BGA25_P0.5,OVM7692-RYAA,OmniVision,Digi-Key,884-1027-1-ND,6.0000,12.0000,
23,1,U4,LSM6DSV16X,"6-axis IMU, LGA-14",Package_LGA:LGA-14_3x2.5mm_P0.5mm_LayoutBorder3x4y,LSM6DSV16XTR,STMicroelectronics,Digi-Key,497-LSM6DSV16XTRCT-ND,4.5000,4.5000,
24,1,U5,Inclinometer,"inclinometer, LGA-16 (stand-in pin map)",gleda:LGA-16_5x5mm_P1.0mm,IIS2ICLXTR,STMicroelectronics,Digi-Key,497-IIS2ICLXTRCT-ND,18.0000,18.0000,
25,1,U6,SPI flash,"SPI NOR flash 64 Mbit, WSON-8 6x5",Package_SON:WSON-8-1EP_6x5mm_P1.27mm_EP3.4x4.3mm,MX25R6435FZNIL0,Macronix,Digi-Key,1092-1187-1-ND,1.6000,1.6000,
26,1,U7,MCP1700-2.8,"LDO 2.8 V, always on",Package_TO_SOT_SMD:SOT-23,MCP1700T-2802E/TT,Microchip,Digi-Key,MCP1700T2802ETTCT-ND,0.4500,0.4500,
27,1,U8,LP5907-2.8,LDO 2.8 V for the cameras,Package_TO_SOT_SMD:SOT-23-5,LP5907MFX-2.8/NOPB,Texas Instruments,Digi-Key,296-38557-1-ND,0.6000,0.6000,
28,1,U9,MCP73831,Li-Po charger,Package_TO_SOT_SMD:SOT-23-5,MCP73831T-2ACI/OT,Microchip,Digi-Key,MCP73831T-2ACI/OTCT-ND,0.7000,0.7000,
29,1,U10,USBLC6-2SC6,USB ESD protection,Package_TO_SOT_SMD:SOT-23-6,USBLC6-2SC6,STMicroelectronics,Digi-Key,497-5235-1-ND,0.4000,0.4000,
30,1,U11,MCP1700-3.3,LDO 3.3 V for VDDUSB,Package_TO_SOT_SMD:SOT-23,MCP1700T-3302E/TT,Microchip,Digi-Key,MCP1700T3302ETTCT-ND,0.4500,0.4500,
31,1,Y1,32.768k,32.768 kHz crystal 3215,Crystal:Crystal_SMD_3215-2Pin_3.2x1.5mm,ABS07-120-32.768KHZ-T,Abracon,Digi-Key,535-11937-1-ND,0.6000,0.6000,

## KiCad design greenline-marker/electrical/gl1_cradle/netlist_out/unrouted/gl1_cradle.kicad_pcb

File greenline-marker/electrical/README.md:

# GL-1 electrical package

DRAFT - being written while the main board is routed; the result table below is filled in
by the layout step when the build has run.  Nothing in this directory has been built.

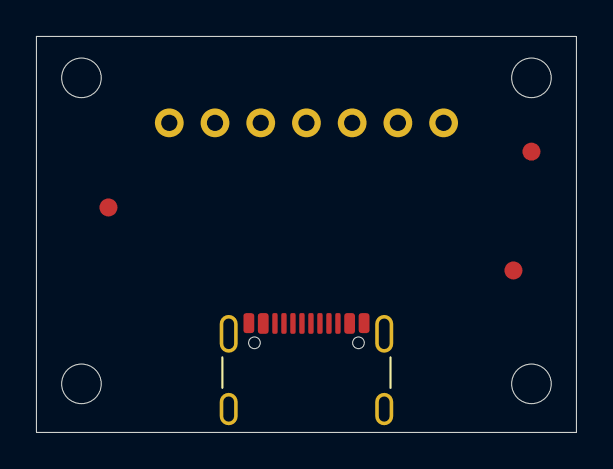
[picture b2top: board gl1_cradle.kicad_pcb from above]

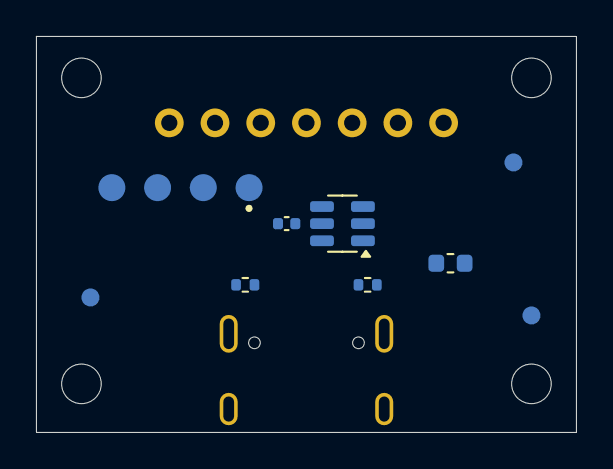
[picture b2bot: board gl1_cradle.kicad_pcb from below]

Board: 2 copper layers, 30.0 x 22.0 mm, 24 parts (9 on the bottom side), 10 nets, no tracks yet.

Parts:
C1: 100n; C_0402_1005Metric
F1: PTC 0.2A; Fuse_0603_1608Metric
FID1, FID2, FID3, FID4, FID5, FID6: Fiducial; Fiducial_1mm_Mask2mm
J1: USB-C; USB_C_Receptacle_GCT_USB4105-xx-A_16P_TopMnt_Horizontal_GL1
J2: Service pads; ServicePads_4x1.5mm_P2.54
MH1, MH2, MH3, MH4: NPTH 2.2mm; NPTH_2.2mm
R1, R2: 5k1; R_0402_1005Metric
SP1, SP2, SP3, SP4, SP5, SP6, SP7: 0914 pin; MillMax_0914_TH_PROVISIONAL
U1: USBLC6-2SC6; SOT-23-6

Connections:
CC1: J1.A5 (CC1), R1.1
CC2: J1.B5 (CC2), R2.1
GND: C1.2, J1.A1 (GND), J1.A12 (GND), J1.S1 (SHIELD), J2.1 (GND), R1.2, R2.2, SP4.1, U1.2 (GND)
NRST: J2.4 (NRST), SP7.1
SWCLK: J2.3 (SWCLK), SP6.1
SWDIO: J2.2 (SWDIO), SP5.1
USB_DM: J1.A7 (DM), J1.B7 (DM), SP2.1, U1.1 (IO1A), U1.6 (IO1B)
USB_DP: J1.A6 (DP), J1.B6 (DP), SP3.1, U1.3 (IO2A), U1.4 (IO2B)
VBUS: F1.2, SP1.1
VBUS_IN: C1.1, F1.1, J1.A4 (VBUS), J1.A9 (VBUS), U1.5 (VBUS)
